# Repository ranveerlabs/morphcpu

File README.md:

# MorphCPU

!!!!not autorouted, details are in routing.md if u think so. hours were already deflated by 100!!!!

just came across a cool analogy that like its pretty similar to how a cafe functions kinda, so i renamed the registers to stuff according to that. i feel like i did a good job haha

anyways MorphCPU is a small processor built from 16 configurable cells on an iCE40UP5K.
The FPGA is on the back of a 70 mm round board, with 16 red LEDs on the front.
Send it 9 bytes over USB and the grid changes what it computes.

If you've poked at a systolic array before, it's close to that. 16 cells, each with an op and a direction. Data walks in from the west and leaves at the east edge over UART. One tick moves it one cell.

It's Verilog for the iCE40UP5K. Python tooling generates the schematic and board layout. Yosys and nextpnr do synthesis and place-and-route.

## why

On a conventional processor, most of the datapath is fixed. Here I can configure 16 cells with an op and a direction, so the values take different routes. I run it at 4 Hz. Four cells takes about a second. At 16 MHz there's nothing to look at.

## the grid

Each cell has a 4-bit configuration: a 2-bit operation and a 2-bit output direction. The four operations are pass, invert, 8-bit add, and XOR. Cells can route north, east, south, or west; inputs that meet at a cell can be combined.

```text
        c0    c1    c2    c3
      +-----+-----+-----+-----+
  r0  |  0  |  1  |  2  |  3  |  -> out
      +-----+-----+-----+-----+
  r1  |  4  |  5  |  6  |  7  |  -> out
      +-----+-----+-----+-----+
  r2  |  8  |  9  | 10  | 11  |  -> out
      +-----+-----+-----+-----+
  r3  | 12  | 13  | 14  | 15  |  -> out
      +-----+-----+-----+-----+
         ^
      data in
```

## a tiny example

Set cell 0 to pass south, cell 4 to add and point east, then cells 5-7 to pass east. Inject 200 on row 0 and 100 on row 1. After stepping through the grid, the UART returns `0x2C`: 300 truncated to 8 bits. The full byte sequence and timing are in the [gateware guide](gateware/README.md#worked-example-add-two-numbers-while-they-travel).

## build and test

You need Icarus Verilog for simulation and OSS CAD Suite for the FPGA bitstream.

```sh
bash gateware/sim/run_sims.sh
bash gateware/build.sh
bash case/export.sh
```

The simulation has 18 passing checks. GitHub Actions also runs the simulations and gateware build on changes; see the [workflow](https://github.com/ranveerlabs/morphcpu/actions/workflows/gateware.yml).

## status

The 4-layer PCB is routed: KiCad reports no violations or unconnected items. The latest recorded bitstream build used 2,020 of 5,280 logic cells and routed at 37.33 MHz against a 16 MHz clock. That build predates two pin-map changes, and the board has not been flashed yet, so those timing numbers are not verification of the current layout. Routing details and pin changes are in [hardware/ROUTING.md](hardware/ROUTING.md).

The board is 70 mm across with a 4×4 LED grid. The case is printable without supports. More board images are in [`docs/img`](docs/img/README.md); the [23-row BOM table](docs/BOM.md#the-parts) and [BOM CSV](hardware/fab_output/morphcpu-bom.csv) list the parts and quantities.

## license

[CERN-OHL-S-2.0](LICENSE). Third-party files retain their own licenses.

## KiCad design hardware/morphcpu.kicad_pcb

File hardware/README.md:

# hardware/

KiCad project for the 4-layer board. It is placed and routed.

Start with [DESIGN.md](DESIGN.md), then see [ROUTING.md](ROUTING.md) for the
routing details.

| | |
|---|---|
| `morphcpu.kicad_sch` | generated. ERC 0/0 |
| `morphcpu.kicad_pcb` | 80 components + 4 mounting holes, 546 tracks, 193 vias |
| `morphcpu.kicad_dru` | JLC rules Board Setup cant express |
| [scripts/](scripts/) | generators |
| `fab_output/` | gerbers drill BOM CPL zip |

The latest DRC run had 0 violations, 0 unconnected items and 0 schematic
mismatches. LED1 uses FPGA pin 45 and LED2 uses pin 42. The schematic, source
netlist and PCF all agree.

`fab_output/` was generated from the routed board, with copper on all four
layers. The updated pin map still needs a bitstream build. See
[ROUTING.md](ROUTING.md).

## board

The board is round, 70 mm across, with four layers. Four M2 holes sit on a 29 mm
radius at 45, 135, 225 and 315 degrees. The case uses the same positions in
[../case/morphcpu_case.scad](../case/morphcpu_case.scad)

I started at 60 mm, but that didnt leave enough room. There are 79 footprints,
including a QFN-48, SSOP-20, SOIC-8 and edge-mounted USB-C, all packed around the
resistor ring.

## before you touch it

1. There are two regulators. The UP5K needs 1.2 V core and 3.3 V I/O.
2. The 1.2 V rail has to come up before 3.3 V. Both regulators run from 5 V in
   parallel, and an RC delay holds 3.3 V off. That means the 3.3 V regulator
   needs an enable pin, so the AMS1117 doesnt work here.
3. The clock comes from an active oscillator. The iCE40 has no crystal amplifier,
   and the SG48 has no XIN/XOUT pins.

citations in [DESIGN.md](DESIGN.md)

## regenerating

Dont hand-edit `.kicad_sch` or the placement. Regenerating replaces them, though
the routed tracks are kept. The commands are in [scripts/](scripts/).

tracked: `*.kicad_pro` `*.kicad_sch` `*.kicad_pcb` `*.kicad_sym` `*.kicad_mod`
`*.kicad_dru` the fab zip the two CSVs. rest regenerates, see
[../.gitignore](../.gitignore)

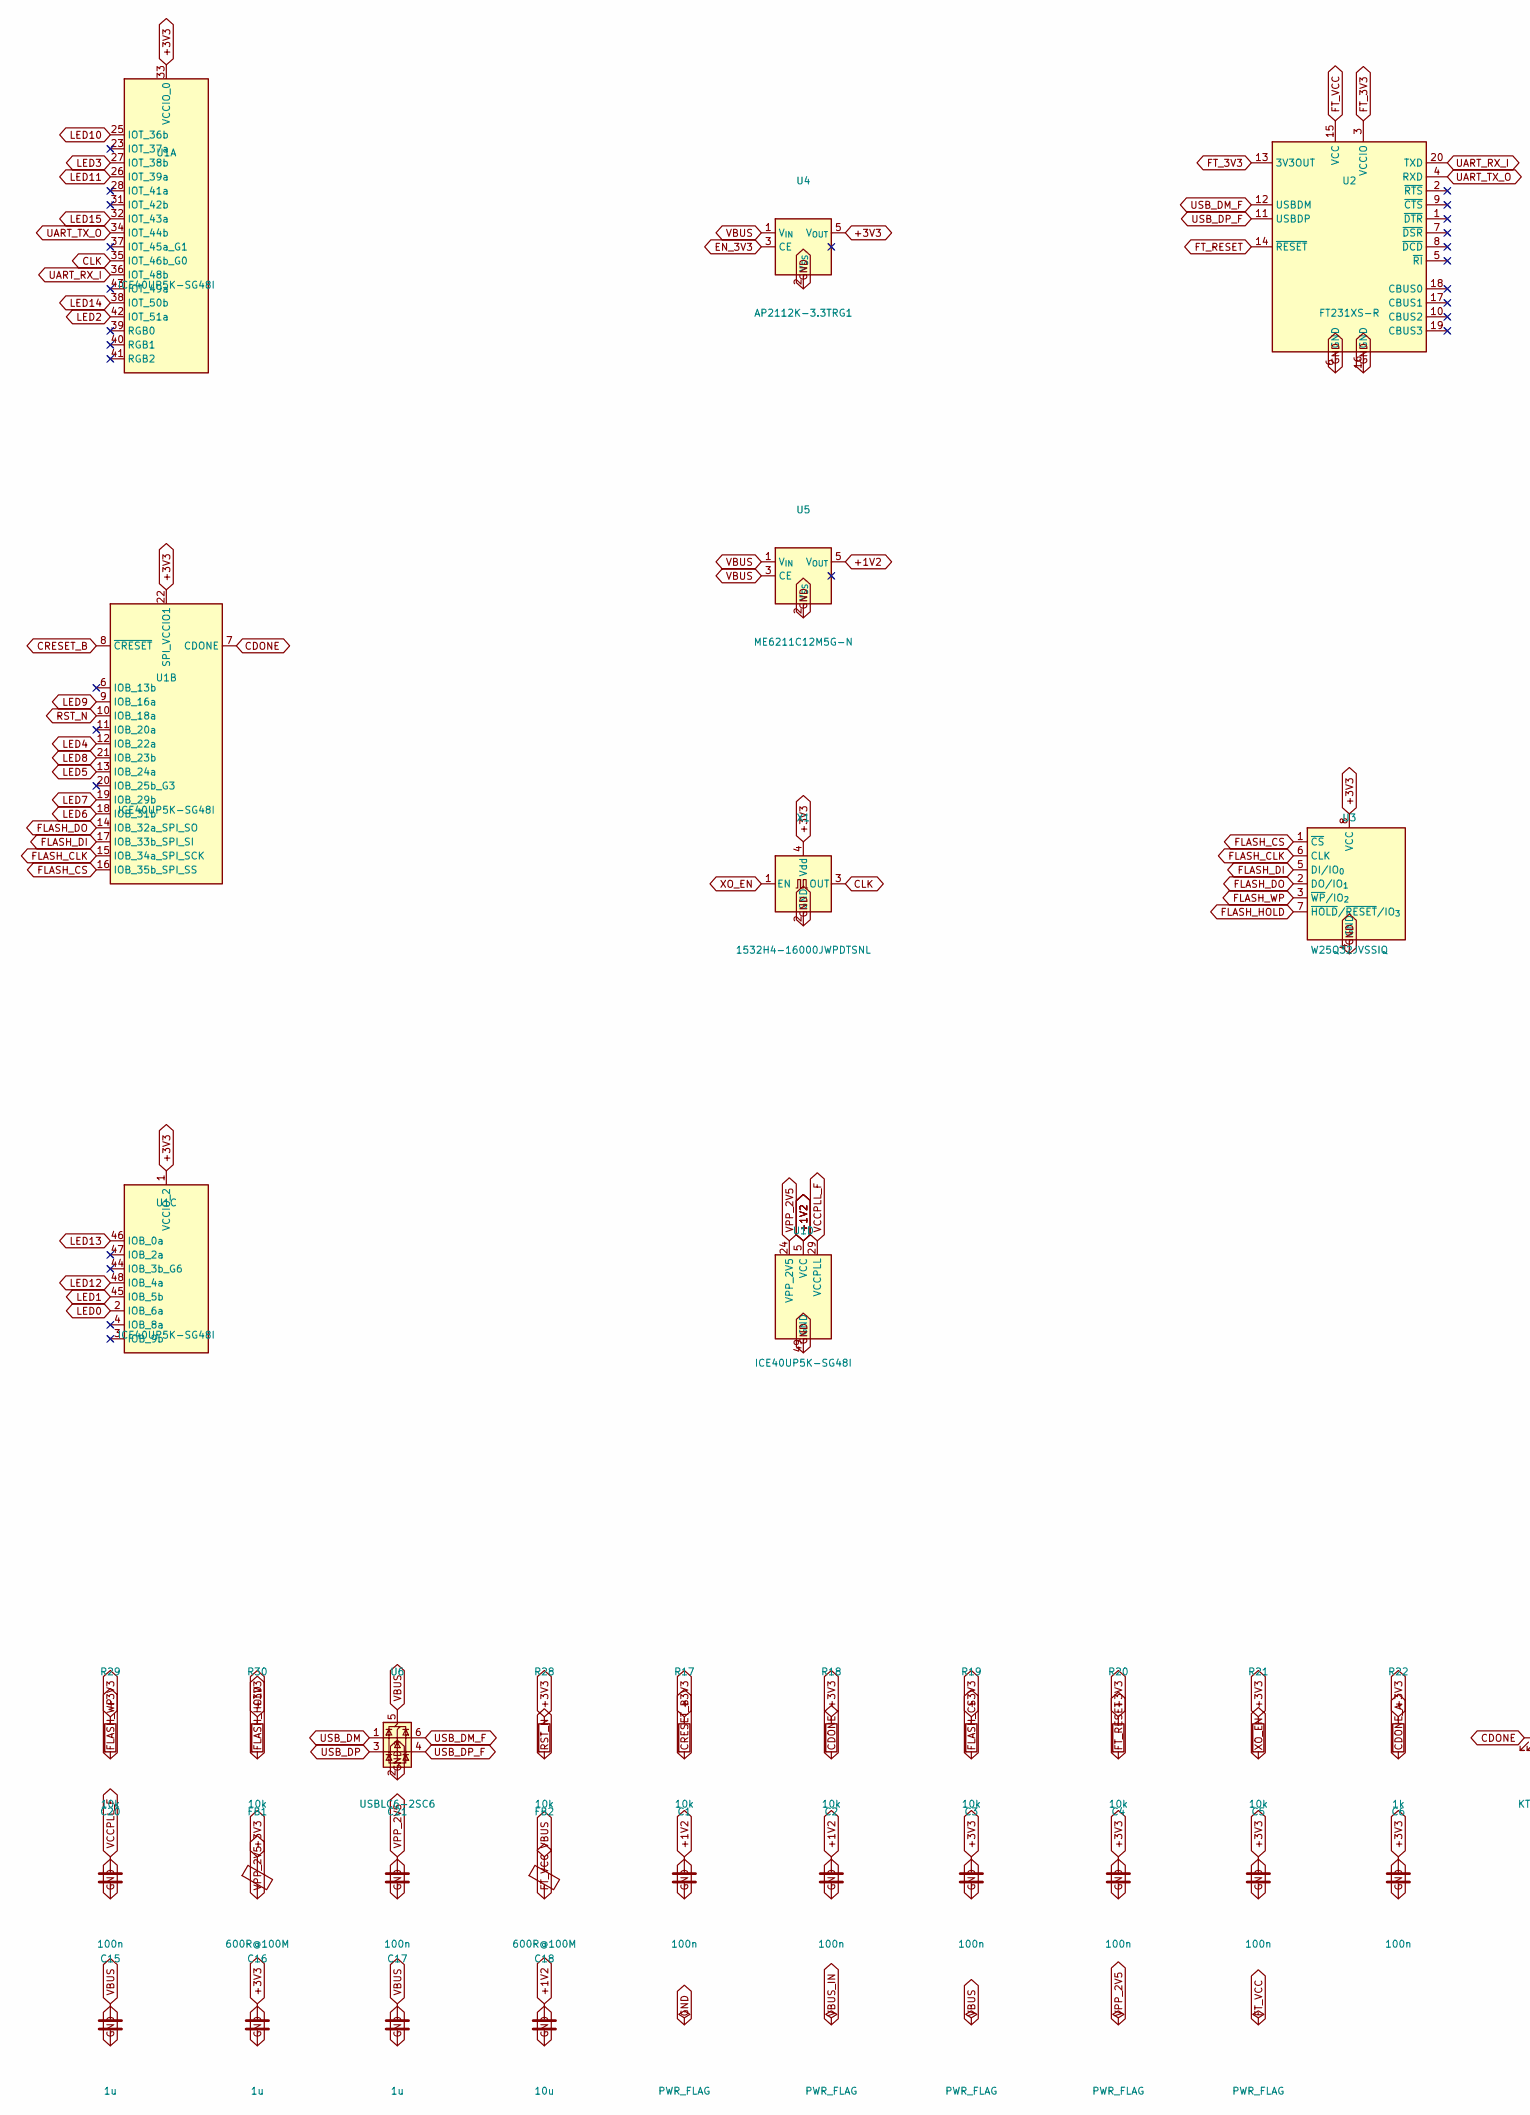
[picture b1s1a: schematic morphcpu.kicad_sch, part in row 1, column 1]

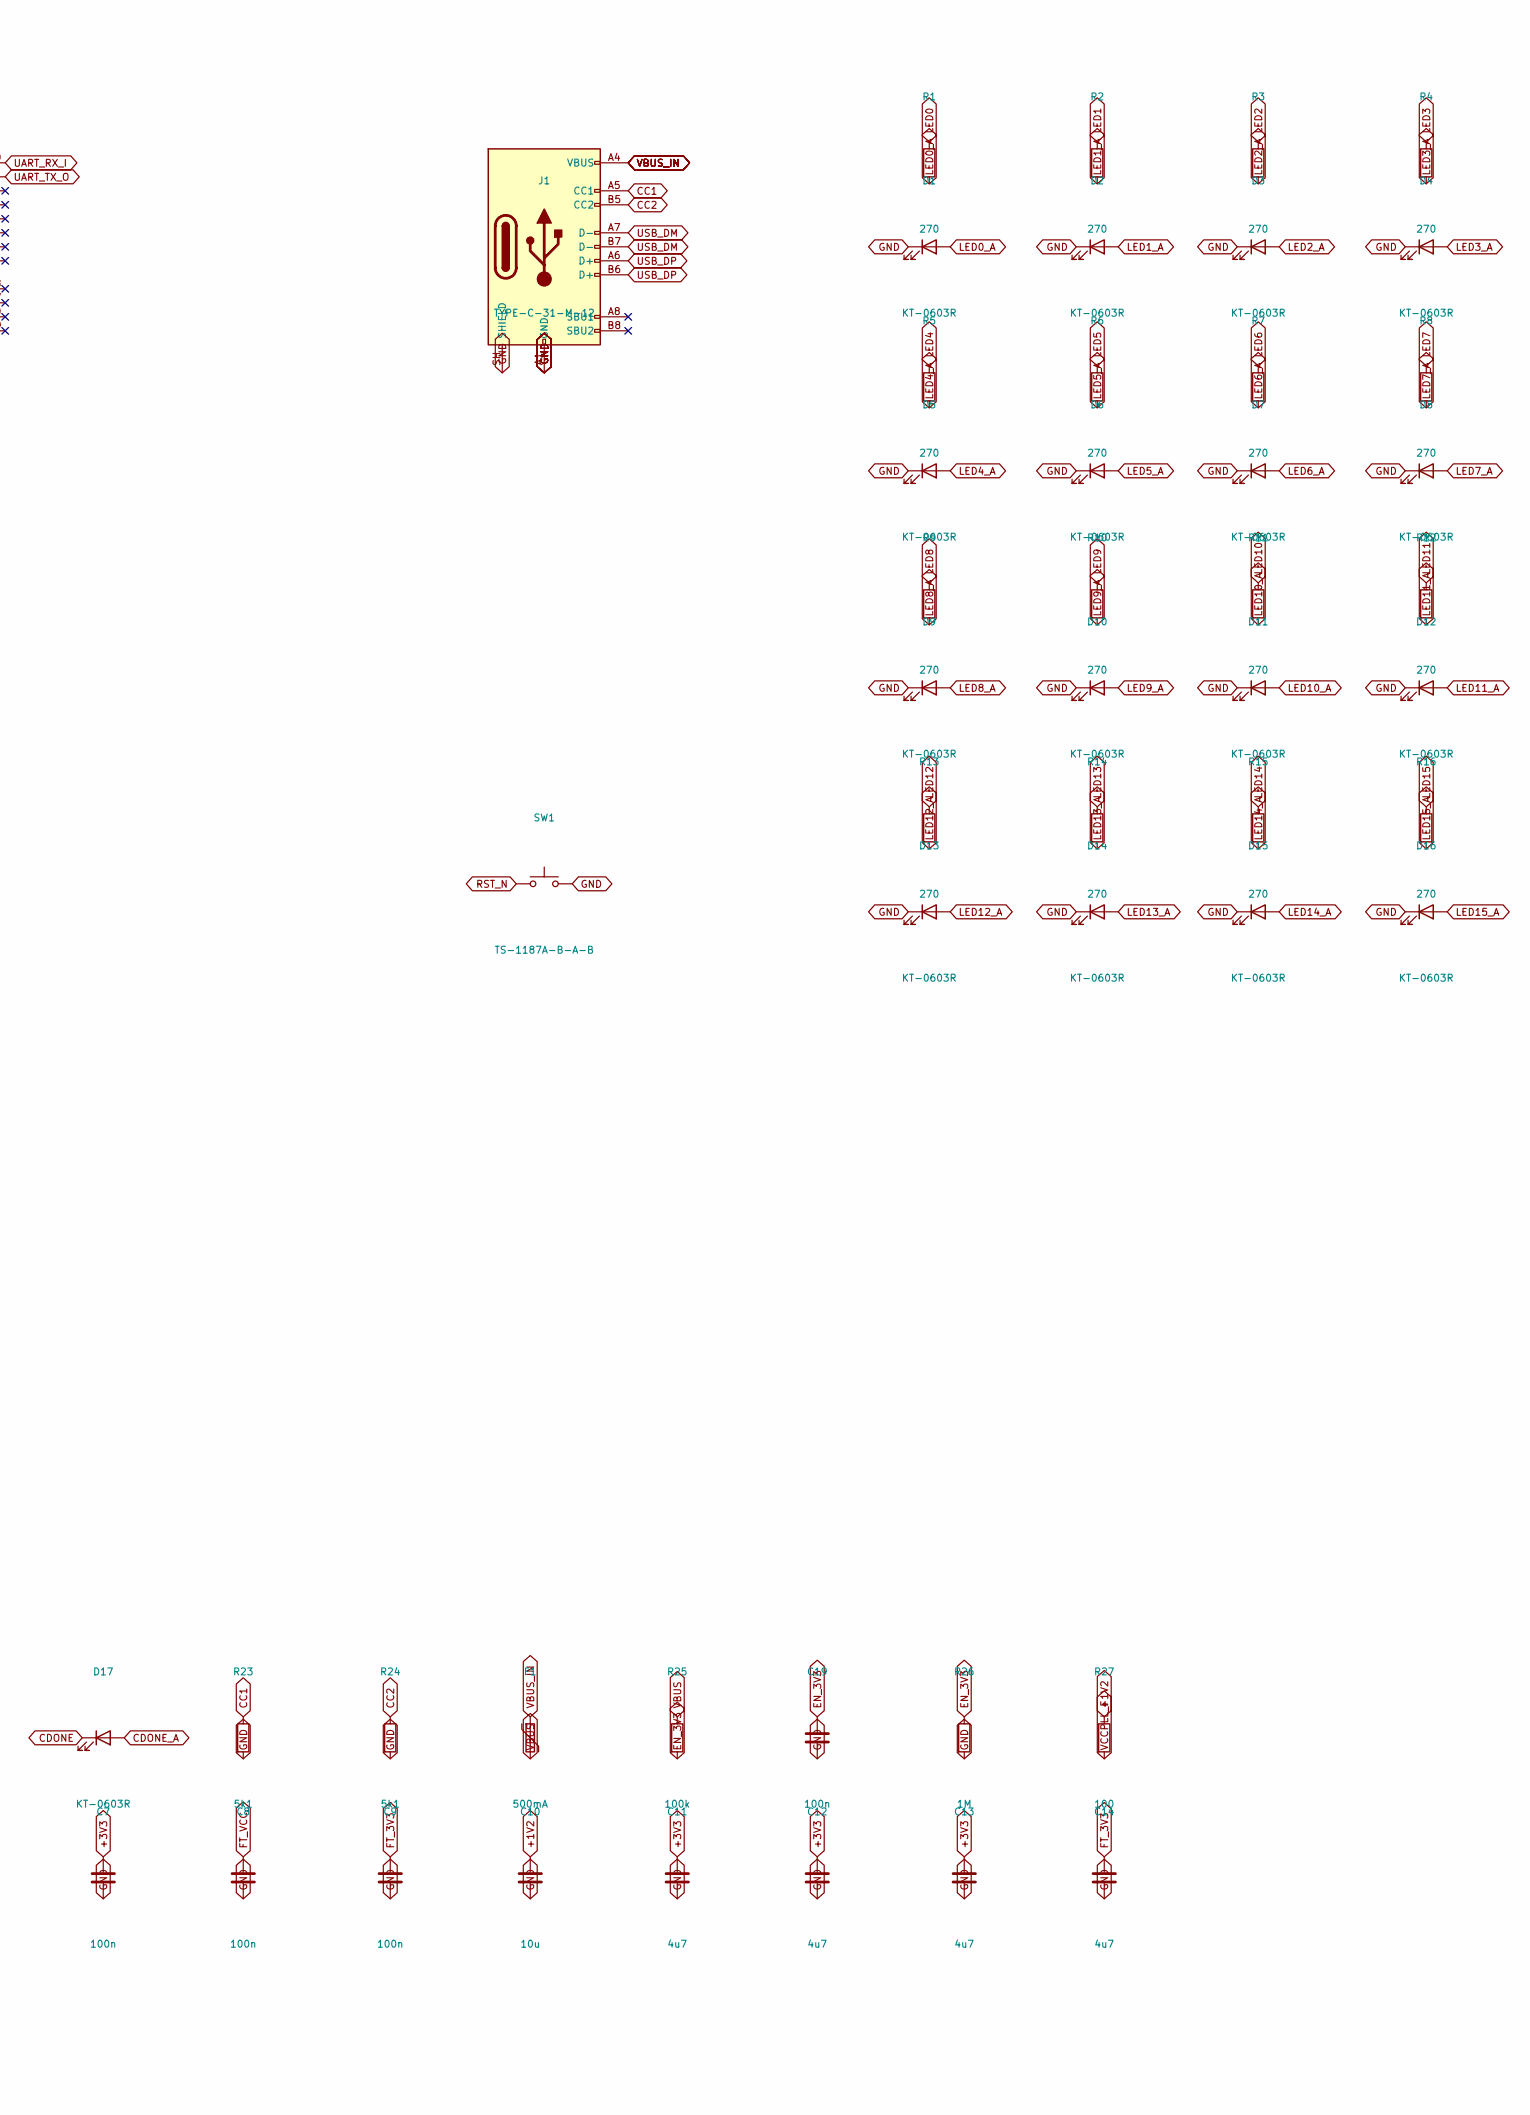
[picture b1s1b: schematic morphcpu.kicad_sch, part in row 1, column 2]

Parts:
C1, C2, C3, C4, C5, C6, C7, C8, C9, C19, C20, C21: 100n; C_0402_1005Metric
C10, C18: 10u; C_0402_1005Metric
C11, C12, C13, C14: 4u7; C_0402_1005Metric
C15, C16, C17: 1u; C_0402_1005Metric
D1, D2, D3, D4, D5, D6, D7, D8, D9, D10, D11, D12, D13, D14, D15, D16, D17: KT-0603R; LED_0603_1608Metric
F1: 500mA; Fuse_1206_3216Metric
FB1, FB2: 600R@100M; L_0603_1608Metric
J1: TYPE-C-31-M-12; USB_C_Receptacle_HRO_TYPE-C-31-M-12
R1, R2, R3, R4, R5, R6, R7, R8, R9, R10, R11, R12, R13, R14, R15, R16: 270; R_0402_1005Metric
R17, R18, R19, R20, R21, R28, R29, R30: 10k; R_0402_1005Metric
R22: 1k; R_0402_1005Metric
R23, R24: 5k1; R_0402_1005Metric
R25: 100k; R_0402_1005Metric
R26: 1M; R_0402_1005Metric
R27: 100; R_0402_1005Metric
SW1: TS-1187A-B-A-B; SW_Push_1P1T_XKB_TS-1187A
U1: ICE40UP5K-SG48I; QFN-48-1EP_7x7mm_P0.5mm_EP5.6x5.6mm
U2: FT231XS-R; SSOP-20_3.9x8.7mm_P0.635mm
U3: W25Q32JVSSIQ; SOIC-8_5.3x5.3mm_P1.27mm
U4: AP2112K-3.3TRG1; SOT-23-5
U5: ME6211C12M5G-N; SOT-23-5
U6: USBLC6-2SC6; SOT-23-6
X1: 1532H4-16000JWPDTSNL; Oscillator_SMD_Abracon_ASE-4Pin_3.2x2.5mm

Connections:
+1V2: C1.1, C2.1, C10.1, C18.1, R27.1, U1.5 (VCC), U1.30 (VCC), U5.5 (V_{OUT})
+3V3: C3.1, C4.1, C5.1, C6.1, C7.1, C11.1, C12.1, C13.1, C16.1, FB1.1, R17.1, R18.1, R19.1, R20.1, R21.1, R22.1, R28.1, R29.1, R30.1, U1.1 (VCCIO_2), U1.22 (SPI_VCCIO1), U1.33 (VCCIO_0), U3.8 (VCC), U4.5 (V_{OUT}), X1.4 (Vdd)
CC1: J1.A5 (CC1), R23.1
CC2: J1.B5 (CC2), R24.1
CDONE: D17.1 (K), R18.2, U1.7 (CDONE)
CDONE_A: D17.2 (A), R22.2
CLK: U1.35 (IOT_46b_G0), X1.3 (OUT)
CRESET_B: R17.2, U1.8 (~CRESET)
EN_3V3: C19.1, R25.2, R26.1, U4.3 (CE)
FLASH_CLK: U1.15 (IOB_34a_SPI_SCK), U3.6 (CLK)
FLASH_CS: R19.2, U1.16 (IOB_35b_SPI_SS), U3.1 (~CS)
FLASH_DI: U1.17 (IOB_33b_SPI_SI), U3.5 (DI/IO_{0})
FLASH_DO: U1.14 (IOB_32a_SPI_SO), U3.2 (DO/IO_{1})
FLASH_HOLD: R30.2, U3.7 (~HOLD/~RESET/IO_{3})
FLASH_WP: R29.2, U3.3 (~WP/IO_{2})
FT_3V3: C9.1, C14.1, U2.3 (VCCIO), U2.13 (3V3OUT)
FT_RESET: R20.2, U2.14 (~RESET)
FT_VCC: C8.1, FB2.2, U2.15 (VCC)
GND: C1.2, C2.2, C3.2, C4.2, C5.2, C6.2, C7.2, C8.2, C9.2, C10.2, C11.2, C12.2, C13.2, C14.2, C15.2, C16.2, C17.2, C18.2, C19.2, C20.2, C21.2, D1.1 (K), D2.1 (K), D3.1 (K), D4.1 (K), D5.1 (K), D6.1 (K), D7.1 (K), D8.1 (K), D9.1 (K), D10.1 (K), D11.1 (K), D12.1 (K), D13.1 (K), D14.1 (K), D15.1 (K), D16.1 (K), J1.A1 (GND), J1.A12 (GND), J1.B1 (GND), J1.B12 (GND), J1.SH (SHIELD), R23.2, R24.2, R26.2, SW1.2, U1.49 (GND), U2.6 (GND), U2.16 (GND), U3.4 (GND), U4.2 (V_{SS}), U5.2 (V_{SS}), U6.2 (GND), X1.2 (GND)
LED0: R1.1, U1.2 (IOB_6a)
LED0_A: D1.2 (A), R1.2
LED1: R2.1, U1.45 (IOB_5b)
LED1_A: D2.2 (A), R2.2
LED2: R3.1, U1.42 (IOT_51a)
LED2_A: D3.2 (A), R3.2
LED3: R4.1, U1.27 (IOT_38b)
LED3_A: D4.2 (A), R4.2
LED4: R5.1, U1.12 (IOB_22a)
LED4_A: D5.2 (A), R5.2
LED5: R6.1, U1.13 (IOB_24a)
LED5_A: D6.2 (A), R6.2
LED6: R7.1, U1.18 (IOB_31b)
LED6_A: D7.2 (A), R7.2
LED7: R8.1, U1.19 (IOB_29b)
LED7_A: D8.2 (A), R8.2
LED8: R9.1, U1.21 (IOB_23b)
LED8_A: D9.2 (A), R9.2
LED9: R10.1, U1.9 (IOB_16a)
LED9_A: D10.2 (A), R10.2
LED10: R11.1, U1.25 (IOT_36b)
LED10_A: D11.2 (A), R11.2
LED11: R12.1, U1.26 (IOT_39a)
LED11_A: D12.2 (A), R12.2
LED12: R13.1, U1.48 (IOB_4a)
LED12_A: D13.2 (A), R13.2
LED13: R14.1, U1.46 (IOB_0a)
LED13_A: D14.2 (A), R14.2
LED14: R15.1, U1.38 (IOT_50b)
LED14_A: D15.2 (A), R15.2
LED15: R16.1, U1.32 (IOT_43a)
LED15_A: D16.2 (A), R16.2
RST_N: R28.2, SW1.1, U1.10 (IOB_18a)
UART_RX_I: U1.36 (IOT_48b), U2.20 (TXD)
UART_TX_O: U1.34 (IOT_44b), U2.4 (RXD)
USB_DM: J1.A7 (D-), J1.B7 (D-), U6.1 (I/O1)
USB_DM_F: U2.12 (USBDM), U6.6 (I/O1)
USB_DP: J1.A6 (D+), J1.B6 (D+), U6.3 (I/O2)
USB_DP_F: U2.11 (USBDP), U6.4 (I/O2)
VBUS: C15.1, C17.1, F1.2, FB2.1, R25.1, U4.1 (V_{IN}), U5.1 (V_{IN}), U5.3 (CE), U6.5 (VBUS)
VBUS_IN: F1.1, J1.A4 (VBUS), J1.A9 (VBUS), J1.B4 (VBUS), J1.B9 (VBUS)
VCCPLL_F: C20.1, R27.2, U1.29 (VCCPLL)
VPP_2V5: C21.1, FB1.2, U1.24 (VPP_2V5)
XO_EN: R21.2, X1.1 (EN)

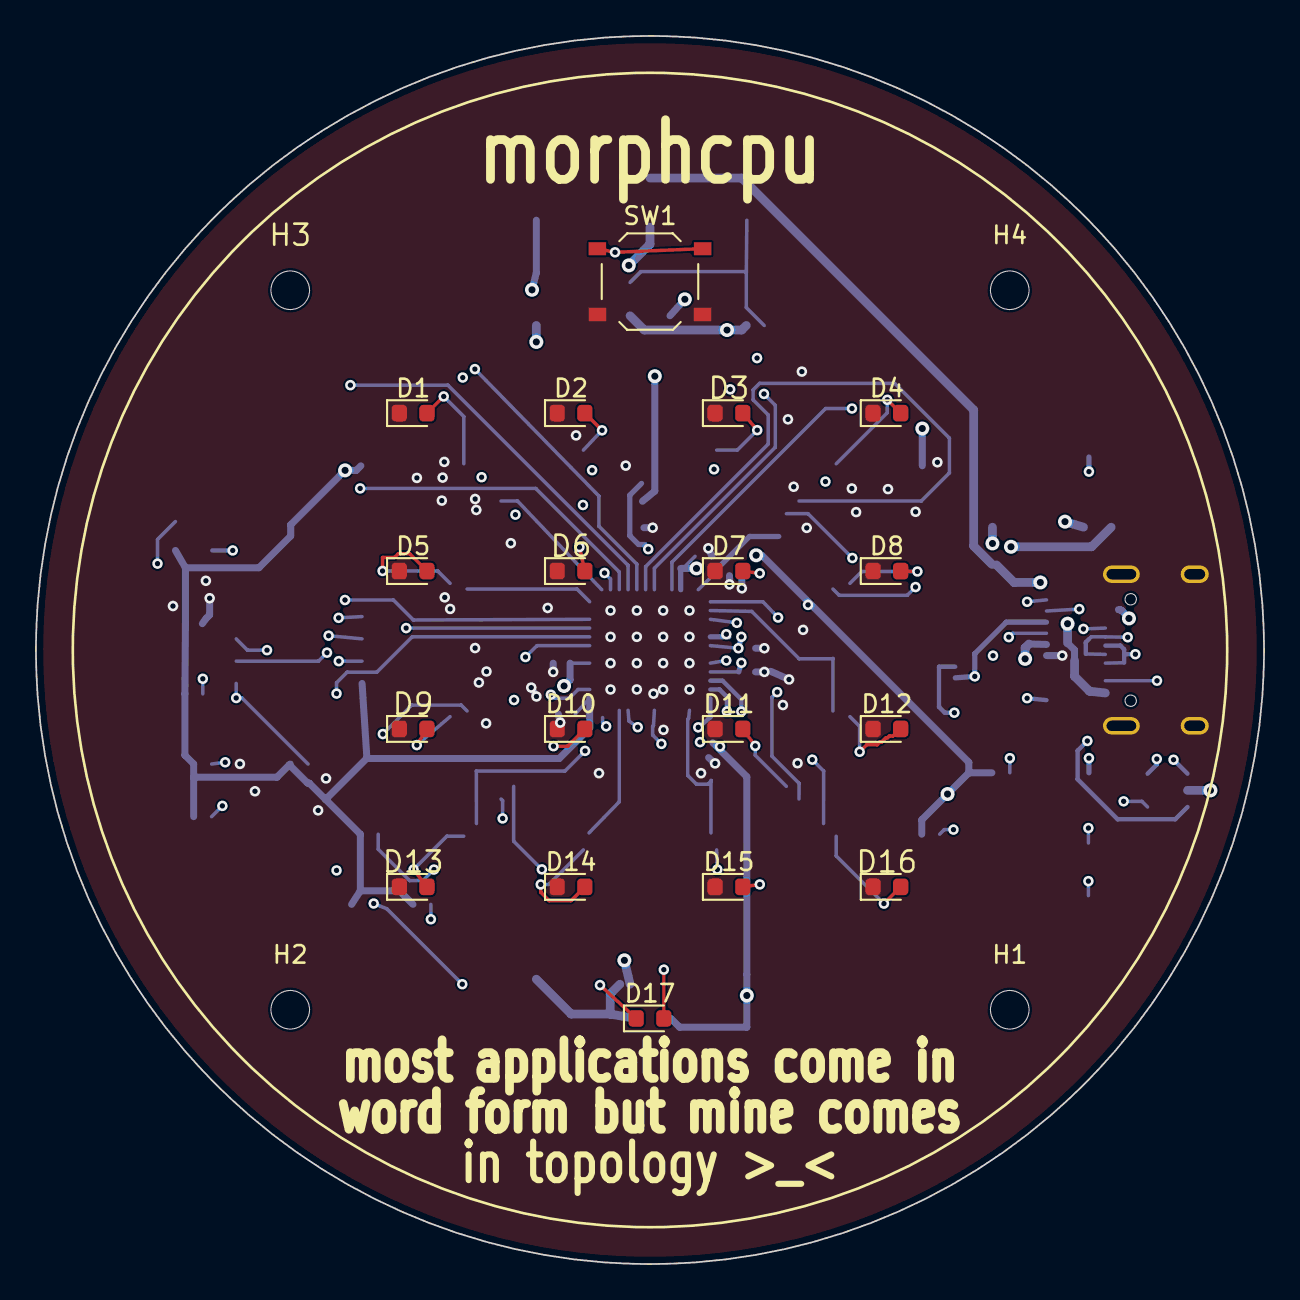
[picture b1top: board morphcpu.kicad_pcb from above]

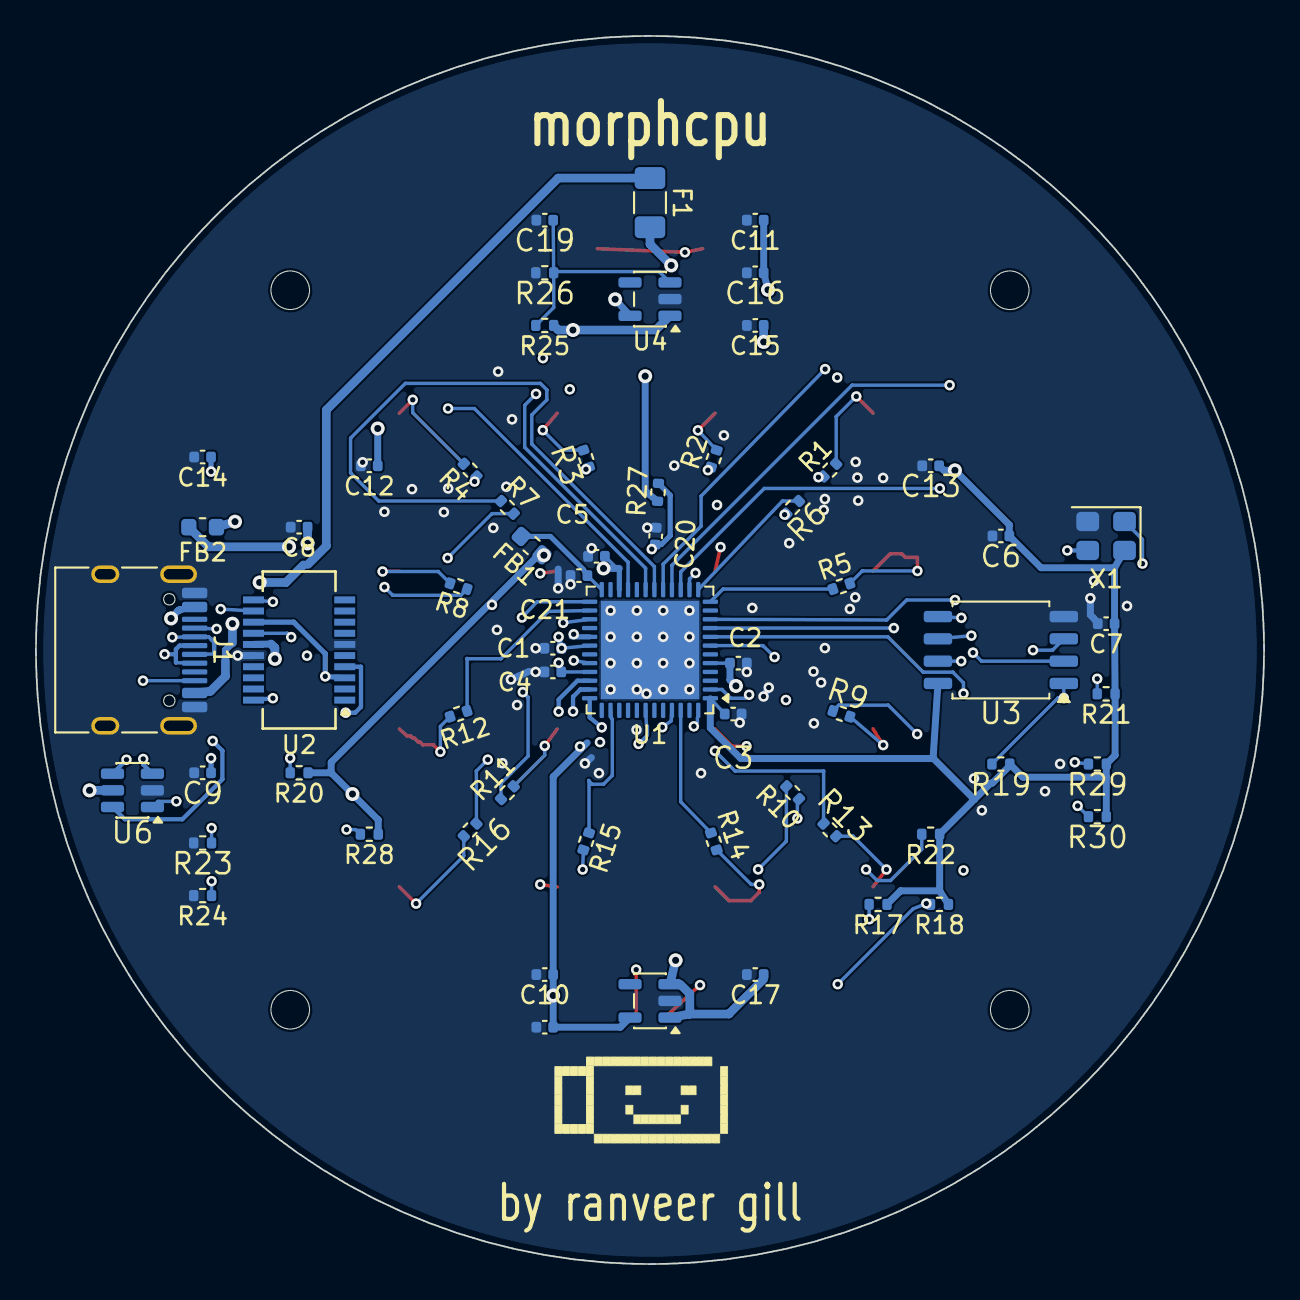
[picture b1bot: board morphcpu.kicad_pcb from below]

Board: 4 copper layers, 70.0 x 70.0 mm, 84 parts (62 on the bottom side), 63 nets.

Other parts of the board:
H1, H2, H3, H4: M2; MountingHole_2.2mm_M2

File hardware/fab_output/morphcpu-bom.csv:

Designator,Quantity,MPN,Comment,Footprint,LCSC Part #
"C1,C2,C3,C4,C5,C6,C7,C8,C9,C19,C20,C21",12,CL05B104KO5NNNC,100n,Capacitor_SMD:C_0402_1005Metric,C1525
"C10,C18",2,CL05A106MQ5NUNC,10u,Capacitor_SMD:C_0402_1005Metric,C15525
"C11,C12,C13,C14",4,CL05A475MP5NRNC,4u7,Capacitor_SMD:C_0402_1005Metric,C23733
"C15,C16,C17",3,CL05A105KA5NQNC,1u,Capacitor_SMD:C_0402_1005Metric,C52923
"D1,D2,D3,D4,D5,D6,D7,D8,D9,D10,D11,D12,D13,D14,D15,D16,D17",17,KT-0603R,KT-0603R,LED_SMD:LED_0603_1608Metric,C2286
F1,1,BSMD1206-050-6V,500mA,Fuse:Fuse_1206_3216Metric,C883122
"FB1,FB2",2,MMZ1608Y601BTA00,600R@100M,Inductor_SMD:L_0603_1608Metric,C136491
J1,1,TYPE-C-31-M-12,TYPE-C-31-M-12,Connector_USB:USB_C_Receptacle_HRO_TYPE-C-31-M-12,C165948
"R1,R2,R3,R4,R5,R6,R7,R8,R9,R10,R11,R12,R13,R14,R15,R16",16,RC0402FR-07270RL,270,Resistor_SMD:R_0402_1005Metric,C163474
"R17,R18,R19,R20,R21,R28,R29,R30",8,0402WGF1002TCE,10k,Resistor_SMD:R_0402_1005Metric,C25744
R22,1,0402WGF1001TCE,1k,Resistor_SMD:R_0402_1005Metric,C11702
"R23,R24",2,0402WGF5101TCE,5k1,Resistor_SMD:R_0402_1005Metric,C25905
R25,1,0402WGF1003TCE,100k,Resistor_SMD:R_0402_1005Metric,C25741
R26,1,0402WGF1004TCE,1M,Resistor_SMD:R_0402_1005Metric,C26083
R27,1,0402WGF1000TCE,100,Resistor_SMD:R_0402_1005Metric,C25076
SW1,1,TS-1187A-B-A-B,TS-1187A-B-A-B,Button_Switch_SMD:SW_Push_1P1T_XKB_TS-1187A,C318884
U1,1,ICE40UP5K-SG48I,ICE40UP5K-SG48I,Package_DFN_QFN:QFN-48-1EP_7x7mm_P0.5mm_EP5.6x5.6mm,C2678152
U2,1,FT231XS-R,FT231XS-R,Package_SO:SSOP-20_3.9x8.7mm_P0.635mm,C132160
U3,1,W25Q32JVSSIQ,W25Q32JVSSIQ,Package_SO:SOIC-8_5.3x5.3mm_P1.27mm,C179173
U4,1,AP2112K-3.3TRG1,AP2112K-3.3TRG1,Package_TO_SOT_SMD:SOT-23-5,C51118
U5,1,ME6211C12M5G-N,ME6211C12M5G-N,Package_TO_SOT_SMD:SOT-23-5,C236672
U6,1,USBLC6-2SC6,USBLC6-2SC6,Package_TO_SOT_SMD:SOT-23-6,C7519
X1,1,1532H4-16000JWPDTSNL,1532H4-16000JWPDTSNL,Oscillator:Oscillator_SMD_Abracon_ASE-4Pin_3.2x2.5mm,C5383161

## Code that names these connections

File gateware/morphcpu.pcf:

set_io -nowarn clk        35

set_io -nowarn rst_n      10

set_io -nowarn uart_tx_o  34
set_io -nowarn uart_rx_i  36

set_io -nowarn led[0]      2
set_io -nowarn led[1]     45
set_io -nowarn led[2]     42
set_io -nowarn led[3]     27
set_io -nowarn led[4]     12
set_io -nowarn led[5]     13
set_io -nowarn led[6]     18
set_io -nowarn led[7]     19
set_io -nowarn led[8]     21
set_io -nowarn led[9]      9
set_io -nowarn led[10]    25
set_io -nowarn led[11]    26
set_io -nowarn led[12]    48
set_io -nowarn led[13]    46
set_io -nowarn led[14]    38
set_io -nowarn led[15]    32
